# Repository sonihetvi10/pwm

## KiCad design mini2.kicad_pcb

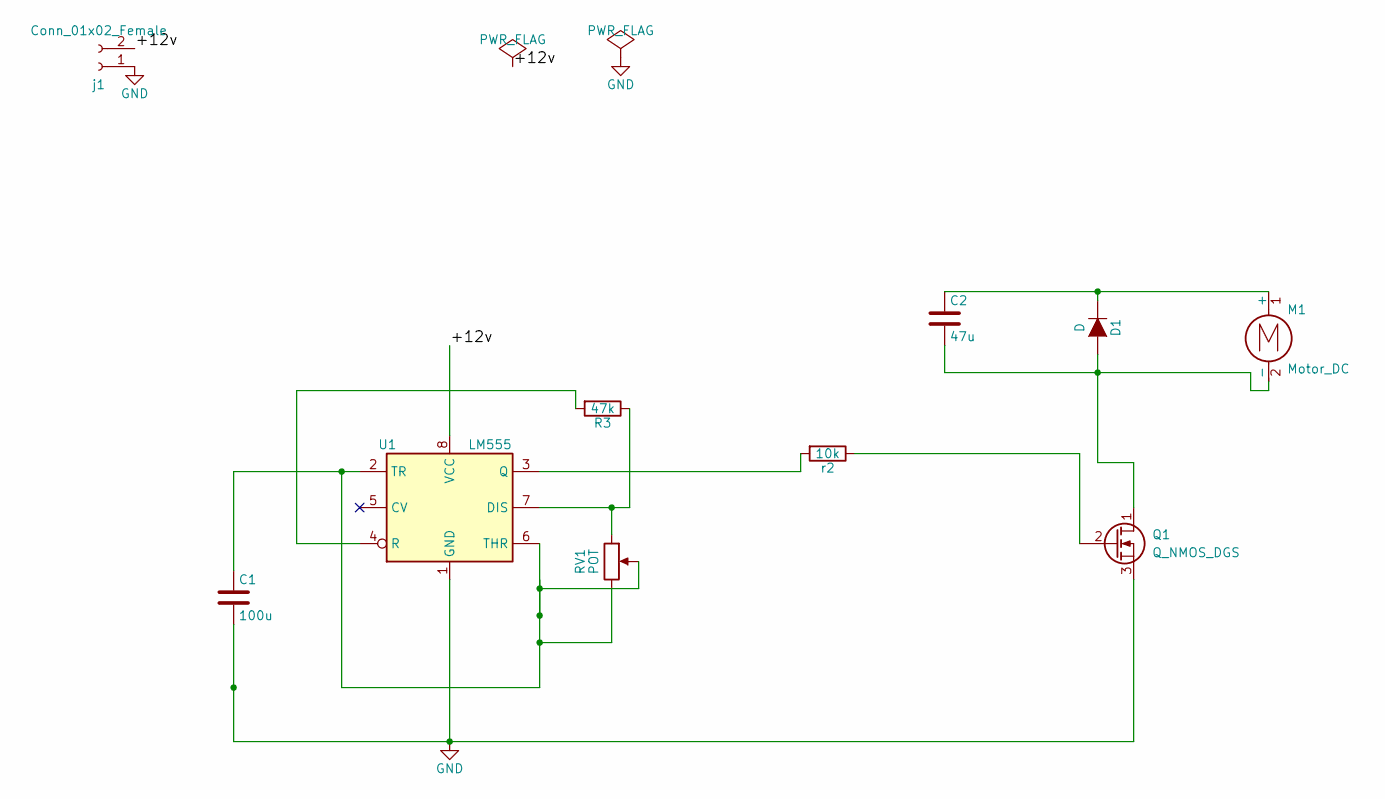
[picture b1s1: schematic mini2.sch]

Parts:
C1: 100u; D_A-405_P5.08mm_Vertical_AnodeUp
C2: 47u; CP_Radial_D18.0mm_P7.50mm
D1: D; D_A-405_P10.16mm_Horizontal
M1: Motor_DC; TerminalBlock_Pheonix_MPT-2.54mm_2pol
Q1: Q_NMOS_DGS; TO-39-3
R3: 47k; R_Axial_DIN0204_L3.6mm_D1.6mm_P5.08mm_Horizontal
RV1: POT; Potentiometer_Omeg_PC16PU_Horizontal
U1: LM555; PDIP-8
j1: Conn_01x02_Female; TerminalBlock_Pheonix_MKDS1.5-2pol
r2: 10k; R_Axial_DIN0204_L3.6mm_D1.6mm_P5.08mm_Horizontal

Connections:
/+12v: U1.8 (VCC), j1.2
GND: C1.2, Q1.3 (S), U1.1 (GND), j1.1
unnamed: C1.1, RV1.2, RV1.3, U1.2 (TR), U1.6 (THR)
unnamed: C2.1, D1.1 (K), M1.1 (+)
unnamed: C2.2, D1.2 (A), M1.2 (-), Q1.1 (D)
unnamed: Q1.2 (G), r2.1
unnamed: R3.1, RV1.1, U1.7 (DIS)
unnamed: R3.2, U1.4 (R)
unnamed: U1.3 (Q), r2.2

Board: 2 copper layers, 10 parts (0 on the bottom side), 9 nets, no tracks yet.
